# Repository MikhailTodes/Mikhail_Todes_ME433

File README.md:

# Advanced Mechatronics Repo

This repository holds the resources and work being done for the Advanced Mechatronics course (ME433) that I am taking.

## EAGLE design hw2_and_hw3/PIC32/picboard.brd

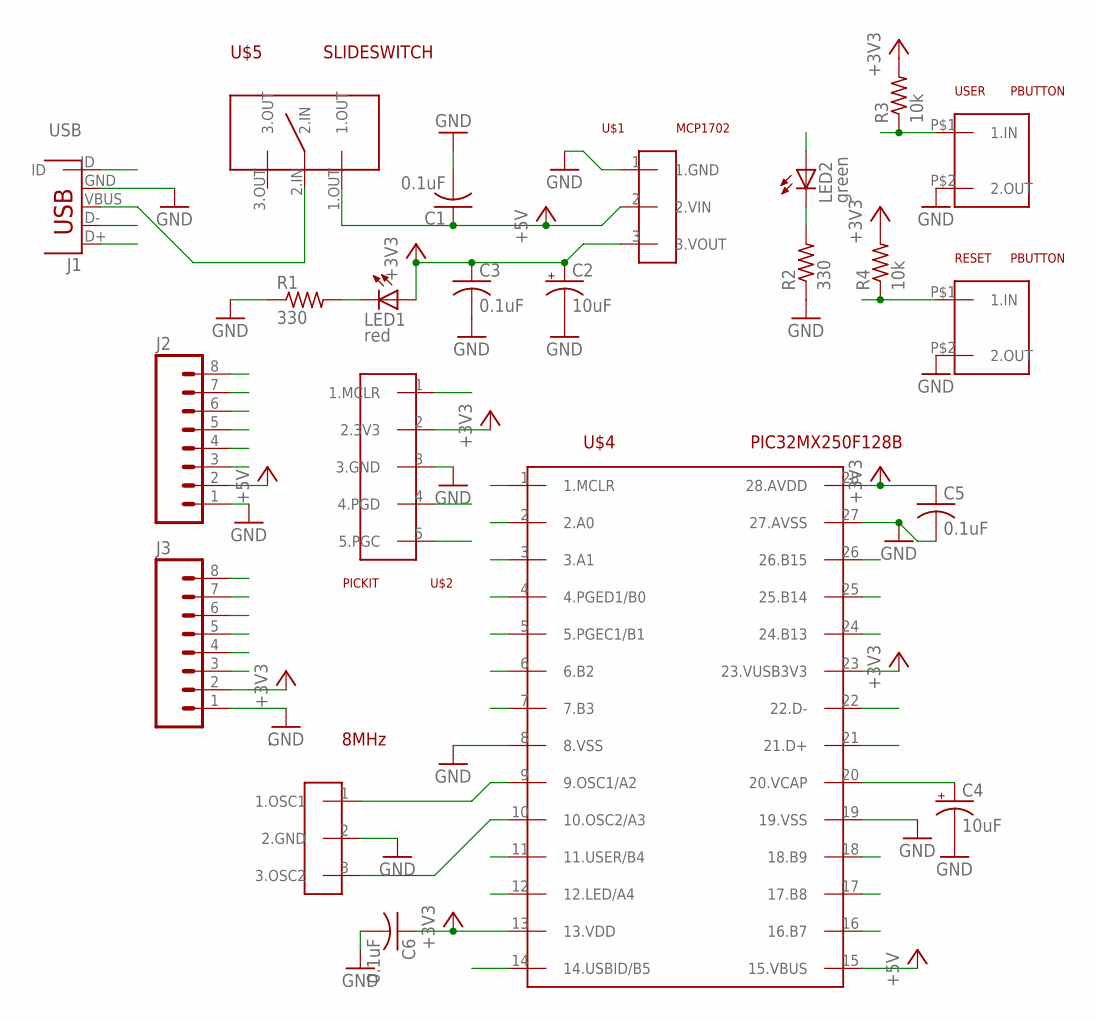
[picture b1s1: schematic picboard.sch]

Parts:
.: 8MHz; 1X03
C1, C3, C5, C6: 0.1uF; C025-025X050
C2, C4: 10uF; B45181A
J1: USB; USB-MB-H
J2, J3: M08; 1X08_ROUND
LED1: red; LED3MM
LED2: green; LED3MM
R1, R2: 330; 0207/10
R3, R4: 10k; 0207/10
RESET: PBUTTON
U$1: MCP1702; TO92
U$2: PICKIT; 1X05
U$4: PIC32MX250F128B; DIL28-3
U$5: SLIDESWITCH
USER: PBUTTON

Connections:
+3V3: C2.+, C3.1, C5.1, C6.1, J3.2, LED1.A, R3.2, R4.2, U$1.3 (3.VOUT), U$2.2 (2.3V3), U$4.13 (13.VDD), U$4.23 (23.VUSB3V3), U$4.28 (28.AVDD)
+5V: C1.1, J2.2, U$1.2 (2.VIN), U$4.15 (15.VBUS), U$5.1.OUT
A0: J3.8, U$4.2 (2.A0)
A1: J3.7, U$4.3 (3.A1)
B2: J3.6, U$4.6 (6.B2)
B3: J3.5, U$4.7 (7.B3)
B7: J2.3, U$4.16 (16.B7)
B8: J2.4, U$4.17 (17.B8)
B9: J2.5, U$4.18 (18.B9)
B13: J2.6, U$4.24 (24.B13)
B14: J2.7, U$4.25 (25.B14)
B15: J2.8, U$4.26 (26.B15)
D+: J1.D+, U$4.21 (21.D+)
D-: J1.D-, U$4.22 (22.D-)
GND: ..2 (2.GND), C1.2, C2.-, C3.2, C4.-, C5.2, C6.2, J1.GND, J2.1, J3.1, R1.1, R2.1, RESET.P$2 (2.OUT), U$1.1 (1.GND), U$2.3 (3.GND), U$4.8 (8.VSS), U$4.19 (19.VSS), U$4.27 (27.AVSS), USER.P$2 (2.OUT)
LED/A4: J3.3, LED2.A, U$4.12 (12.LED/A4)
MCLR: R4.1, RESET.P$1 (1.IN), U$2.1 (1.MCLR), U$4.1 (1.MCLR)
unnamed: J1.VBUS, U$5.2.IN
unnamed: LED1.K (C), R1.2
unnamed: LED2.K (C), R2.2
unnamed: C4.+, U$4.20 (20.VCAP)
unnamed: ..1 (1.OSC1), U$4.9 (9.OSC1/A2)
unnamed: ..3 (3.OSC2), U$4.10 (10.OSC2/A3)
PGC: U$2.5 (5.PGC), U$4.5 (5.PGEC1/B1)
PGD: U$2.4 (4.PGD), U$4.4 (4.PGED1/B0)
USBID: J1.ID, U$4.14 (14.USBID/B5)
USER/B4: J3.4, R3.1, U$4.11 (11.USER/B4), USER.P$1 (1.IN)

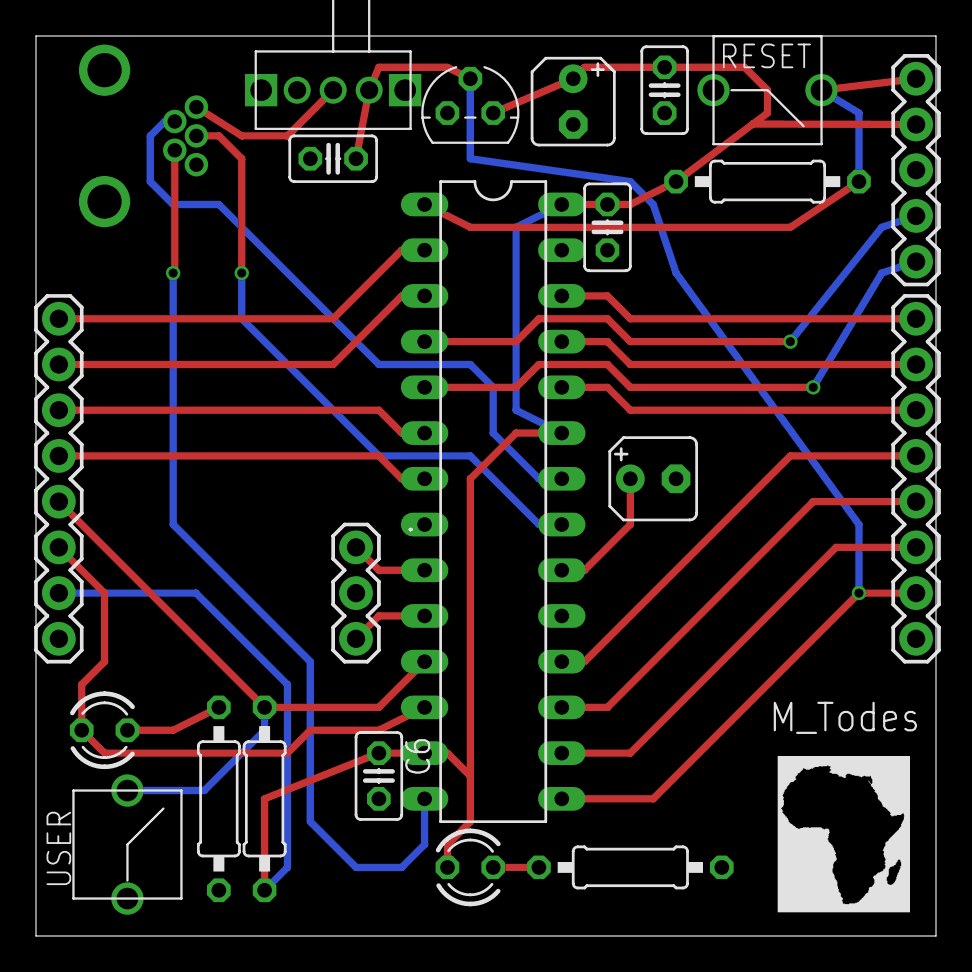
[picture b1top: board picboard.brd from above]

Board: 2 copper layers, 50.0 x 50.0 mm, 22 parts (0 on the bottom side), 27 nets.

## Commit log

2016-03-31 Set Up
2016-04-02 Added screenshot of pre cap oscilations on regulator output
2016-04-02 Added pic of finished breadboard circuit
2016-04-02 Cropped image of finished breadboard
2016-04-03 Added new project file with empty main.c for PIC32 programming
2016-04-03 Added template to main.c --> Still need to fill in PRAGMA values
2016-04-03 Filled in DEVCFG0 pragma values
2016-04-03 Filled out DEVCFG1 pragmas
2016-04-03 Completed pragma configurations
2016-04-03 Built and programmed pic to toggle green LED on user push button
2016-04-04 Finished HW1, LED toggling at 1000Hz and stopped when push button pressed
2016-04-12 added new eagle project for PCB design
2016-04-13 Added start of schematic. Still need to finish a few connections
2016-04-13 added complete library
2016-04-14 Finished schematic
2016-04-14 Added right size brd. Still nee to populate then route
2016-04-14 finished PCB .brd layout. Still need to error check
2016-04-14 Adding grphics to pcb. Error checking done
2016-04-14 Added Africa Graphic
2016-04-14 Bigger graphic
2016-04-14 Clean up labels
2016-04-14 Ready to be checked before order
2016-04-14 Added stormtrooper graphic
2016-04-14 Added Storm Trooper Graphic
2016-04-25 Start setting up for SPI and I2C homework
2016-04-25 Working sin wave
2016-04-25 Added image of osciliscope with sin and triangle waves
2016-04-26 Fixed bug
2016-04-26 Added the I2C setup files. Still need to configure them to use I2c 2
2016-04-26 Eddited I2C setup files
2016-04-27 Edit i2c setup
2016-04-27 Still need to fix I2c
2016-04-27 Testing I2C
2016-05-01 Finished HW4
2016-05-02 File restructure
2016-05-02 Start IMU homework. WHO_AM_I register returning correct value
2016-05-03 Added an initialise function for PWM outputs
2016-05-05 Eddited I2C comms for multiple reads
2016-05-20 Home work 5 - Working LCD screen
2016-05-20 Writing IMU data to the LCD screen and saved pic
2016-05-24 Fixed PWM calculations and added photos
2016-05-30 Added Stl for wheel hw10
2016-05-31 Added pictures of homework 10 and 11
2016-05-31 Cropping images
2016-05-31 Finished hw7 - USB mouse based on IMU read
2016-05-31 Tested new board with blinky light program
2016-06-02 Finished hw9
2016-06-02 add image of workking slider app
2016-06-07 Working camera app with sliders. Need to fix cdc sending
2016-06-08 Added pic code for tech cup and final tech cup app
2016-06-08 Fniished homework 8
